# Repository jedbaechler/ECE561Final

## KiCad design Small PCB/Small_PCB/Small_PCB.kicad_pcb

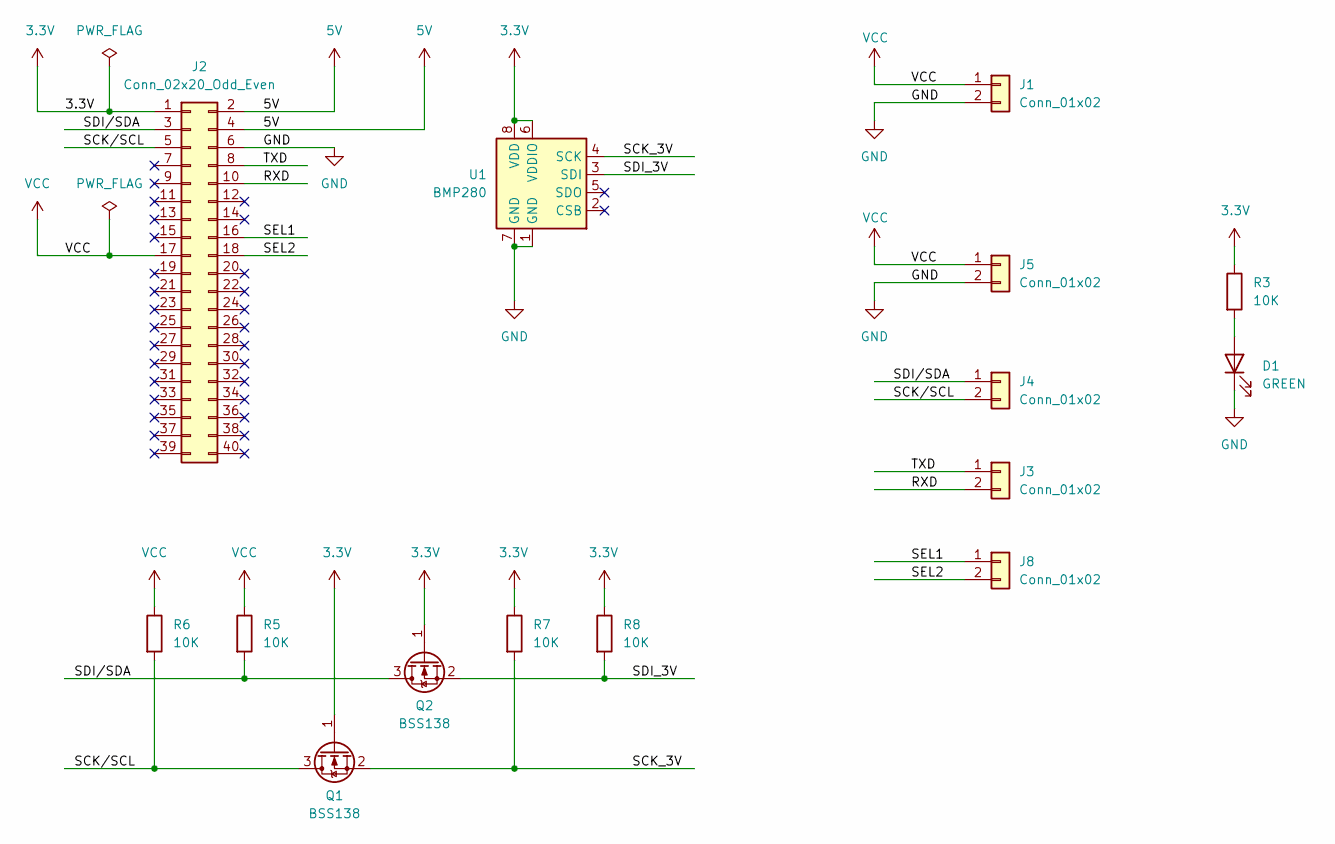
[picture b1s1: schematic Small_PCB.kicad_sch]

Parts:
D1: GREEN; LED_0805_2012Metric
J1, J3, J4, J5, J8: Conn_01x02; JST_EH_B2B-EH-A_1x02_P2.50mm_Vertical
J2: Conn_02x20_Odd_Even; PinSocket_2x20_P2.54mm_Vertical
Q1, Q2: BSS138; SOT-23
R3, R5, R6, R7, R8: 10K; R_0201_0603Metric
U1: BMP280; Bosch_LGA-8_2x2.5mm_P0.65mm_ClockwisePinNumbering

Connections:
3.3V: J2.1, Q1.1 (G), Q2.1 (G), R3.1, R7.1, R8.1, U1.6 (VDDIO), U1.8 (VDD)
5V: J2.2, J2.4
/RXD: J2.10, J3.2
/SCK_3V: Q1.2 (S), R7.2, U1.4 (SCK)
/SCK/SCL: J2.5, J4.2, Q1.3 (D), R6.2
/SDI_3V: Q2.2 (S), R8.2, U1.3 (SDI)
/SDI/SDA: J2.3, J4.1, Q2.3 (D), R5.2
/SEL1: J2.16, J8.1
/SEL2: J2.18, J8.2
/TXD: J2.8, J3.1
GND: D1.1 (K), J1.2, J2.6, J5.2, U1.1 (GND), U1.7 (GND)
unnamed: D1.2 (A), R3.2
VCC: J1.1, J2.17, J5.1, R5.1, R6.1

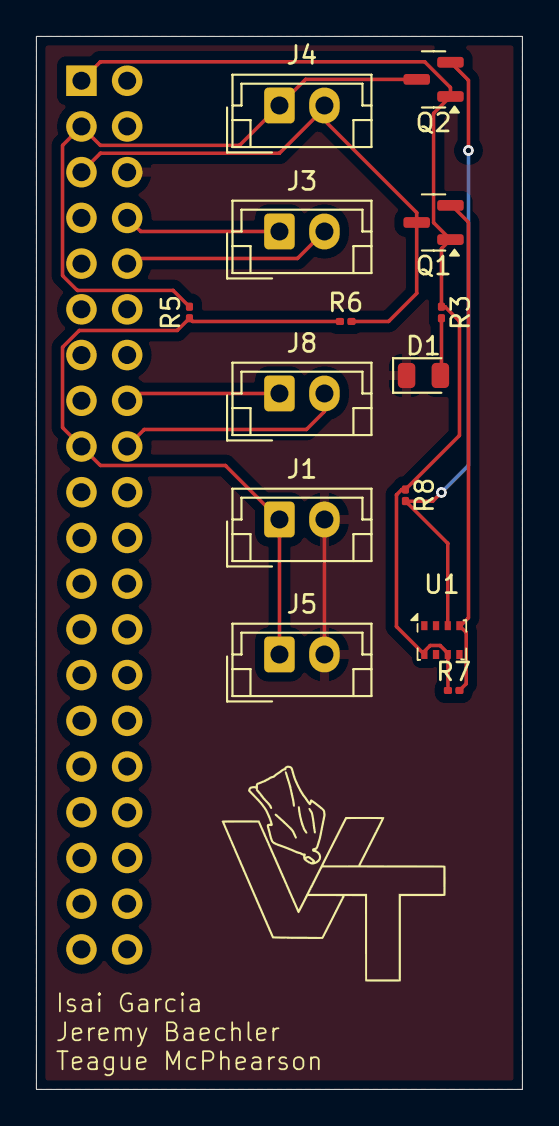
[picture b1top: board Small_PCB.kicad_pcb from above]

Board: 2 copper layers, 27.0 x 58.5 mm, 15 parts (1 on the bottom side), 13 nets.

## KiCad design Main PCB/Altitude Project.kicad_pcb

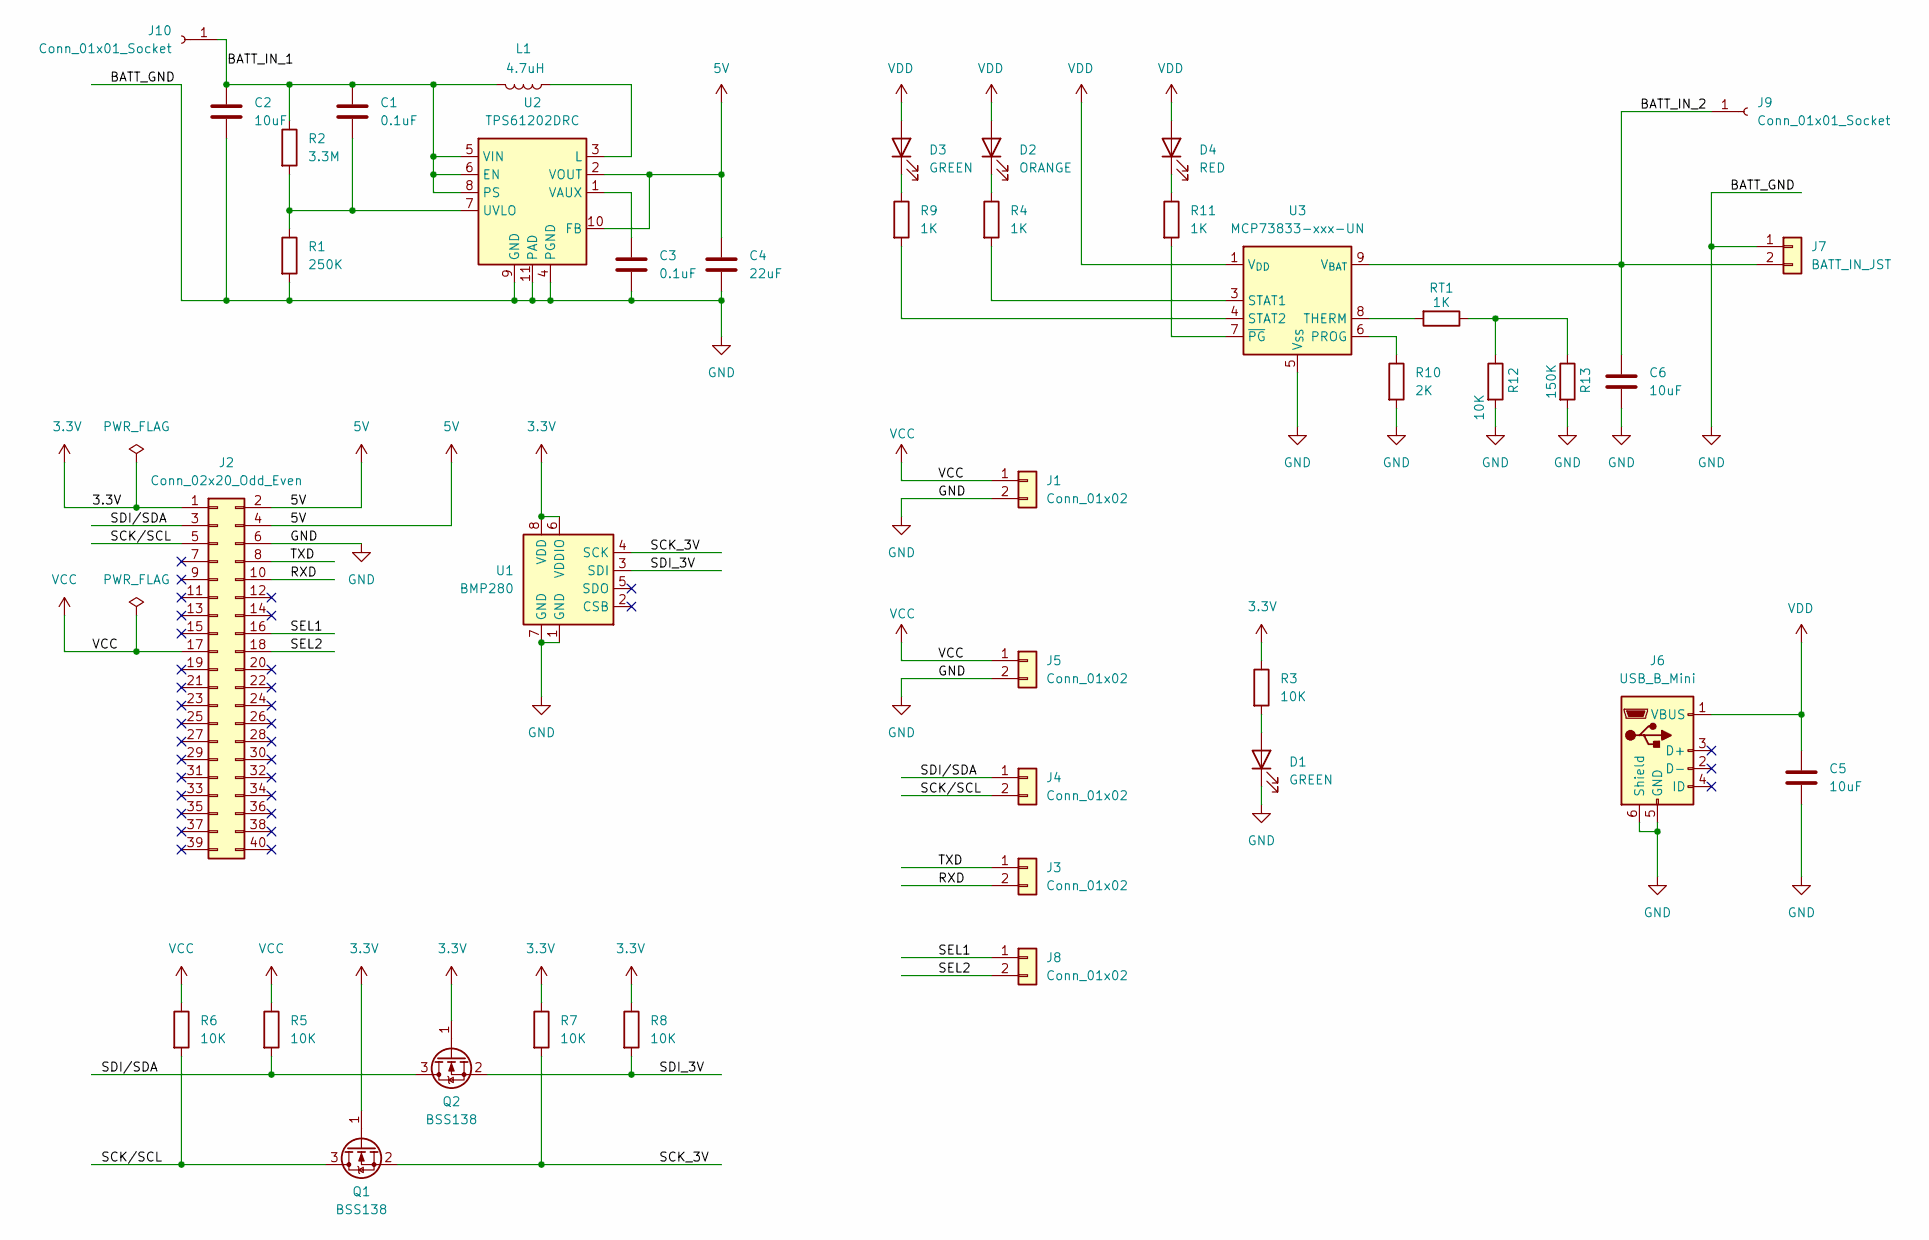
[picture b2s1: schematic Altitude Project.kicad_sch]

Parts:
C1, C3: 0.1uF; C_0402_1005Metric
C2, C5, C6: 10uF; C_0402_1005Metric
C4: 22uF; C_0402_1005Metric
D1, D3: GREEN; LED_0805_2012Metric
D2: ORANGE; LED_0805_2012Metric
D4: RED; LED_0805_2012Metric
J1, J3, J4, J5, J8: Conn_01x02; JST_EH_B2B-EH-A_1x02_P2.50mm_Vertical
J2: Conn_02x20_Odd_Even; PinSocket_2x20_P2.54mm_Vertical
J6: USB_B_Mini; USB_Mini-B_Lumberg_2486_01_Horizontal
J7: BATT_IN_JST; JST_EH_S2B-EH_1x02_P2.50mm_Horizontal
J9, J10: Conn_01x01_Socket; TestPoint_THTPad_2.0x2.0mm_Drill1.0mm
L1: 4.7uH; L_Changjiang_FNR4020S
Q1, Q2: BSS138; SOT-23
R1: 250K; R_0201_0603Metric
R2: 3.3M; R_1206_3216Metric
R3, R5, R6, R7, R8, R12: 10K; R_0201_0603Metric
R4, R9, R11: 1K; R_0201_0603Metric
R10: 2K; R_0201_0603Metric
R13: 150K; R_0201_0603Metric
RT1: 1K; R_0201_0603Metric
U1: BMP280; Bosch_LGA-8_2x2.5mm_P0.65mm_ClockwisePinNumbering
U2: TPS61202DRC; Texas_S-PVSON-N10_ThermalVias
U3: MCP73833-xxx-UN; MSOP-10_3x3mm_P0.5mm

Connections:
3.3V: J2.1, Q1.1 (G), Q2.1 (G), R3.1, R7.1, R8.1, U1.6 (VDDIO), U1.8 (VDD)
5V: C4.1, J2.2, J2.4, U2.2 (VOUT), U2.10 (FB)
/BATT_IN_1: C1.1, C2.1, J10.1, L1.2, R2.1, U2.5 (VIN), U2.6 (EN), U2.8 (PS)
/BATT_IN_2: C6.1, J7.2, J9.1, U3.9 (V_{BAT}), U3.10 (V_{BAT})
/RXD: J2.10, J3.2
/SCK_3V: Q1.2 (S), R7.2, U1.4 (SCK)
/SCK/SCL: J2.5, J4.2, Q1.3 (D), R6.2
/SDI_3V: Q2.2 (S), R8.2, U1.3 (SDI)
/SDI/SDA: J2.3, J4.1, Q2.3 (D), R5.2
/SEL1: J2.16, J8.1
/SEL2: J2.18, J8.2
/TXD: J2.8, J3.1
GND: C2.2, C3.2, C4.2, C5.2, C6.2, D1.1 (K), J1.2, J2.6, J5.2, J6.5 (GND), J6.6 (Shield), J7.1, R1.2, R10.2, R12.2, R13.2, U1.1 (GND), U1.7 (GND), U2.4 (PGND), U2.9 (GND), U2.11 (PAD), U3.5 (V_{SS})
unnamed: D1.2 (A), R3.2
unnamed: D2.1 (K), R4.1
unnamed: D3.1 (K), R9.1
unnamed: D4.1 (K), R11.1
unnamed: R12.1, R13.1, RT1.1
unnamed: L1.1, U2.3 (L)
unnamed: C1.2, R1.1, R2.2, U2.7 (UVLO)
unnamed: C3.1, U2.1 (VAUX)
unnamed: R10.1, U3.6 (PROG)
unnamed: R4.2, U3.3 (STAT1)
unnamed: R9.2, U3.4 (STAT2)
unnamed: RT1.2, U3.8 (THERM)
unnamed: R11.2, U3.7 (~PG)
VCC: J1.1, J2.17, J5.1, R5.1, R6.1
VDD: C5.1, D2.2 (A), D3.2 (A), D4.2 (A), J6.1 (VBUS), U3.1 (V_{DD}), U3.2 (V_{DD})

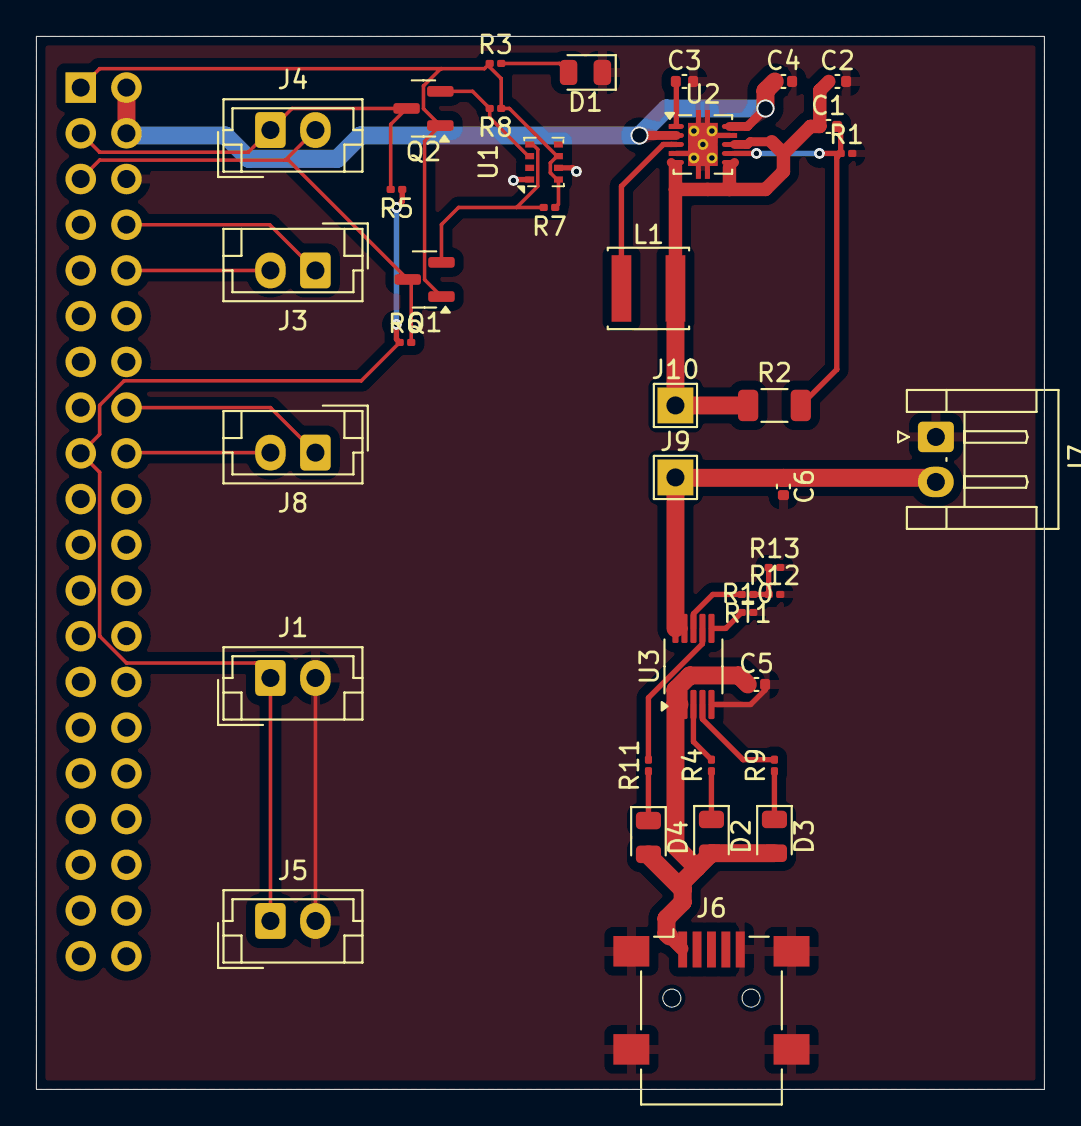
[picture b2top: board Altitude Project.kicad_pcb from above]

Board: 2 copper layers, 56.0 x 58.5 mm, 40 parts (1 on the bottom side), 28 nets.

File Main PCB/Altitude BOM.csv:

"Id";"Designator";"Footprint";"Quantity";"Designation";"Supplier and ref";
1;"U2";"Texas_S-PVSON-N10_ThermalVias";1;"TPS61202DRC";;;
2;"J9,J10";"TestPoint_THTPad_2.0x2.0mm_Drill1.0mm";2;"Conn_01x01_Socket";;;
3;"U3";"MSOP-10_3x3mm_P0.5mm";1;"MCP73833-xxx-UN";;;
4;"C3,C1";"C_0402_1005Metric";2;"0.1uF";;;
5;"R13";"R_0201_0603Metric";1;"150K";;;
6;"L1";"L_Changjiang_FNR4020S";1;"4.7uH";;;
7;"R12,R5,R8,R7,R3,R6";"R_0201_0603Metric";6;"10K";;;
8;"J7";"JST_EH_S2B-EH_1x02_P2.50mm_Horizontal";1;"BATT_IN_JST";;;
9;"U1";"Bosch_LGA-8_2x2.5mm_P0.65mm_ClockwisePinNumbering";1;"BMP280";;;
10;"Q1,Q2";"SOT-23";2;"BSS138";;;
11;"J8,J5,J1,J3,J4";"JST_EH_B2B-EH-A_1x02_P2.50mm_Vertical";5;"Conn_01x02";;;
12;"R4,R11,RT1,R9";"R_0201_0603Metric";4;"1K";;;
13;"R2";"R_1206_3216Metric";1;"3.3M";;;
14;"D3,D1";"LED_0805_2012Metric";2;"GREEN";;;
15;"C4";"C_0402_1005Metric";1;"22uF";;;
16;"D2";"LED_0805_2012Metric";1;"ORANGE";;;
17;"C6,C5,C2";"C_0402_1005Metric";3;"10uF";;;
18;"D4";"LED_0805_2012Metric";1;"RED";;;
19;"R10";"R_0201_0603Metric";1;"2K";;;
20;"R1";"R_0201_0603Metric";1;"250K";;;
21;"J6";"USB_Mini-B_Lumberg_2486_01_Horizontal";1;"USB_B_Mini";;;
22;"J2";"PinSocket_2x20_P2.54mm_Vertical";1;"Conn_02x20_Odd_Even";;;

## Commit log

2024-05-05 Final Code and Schematic Upload
2024-05-05 Suppl. Materials
2024-05-05 final submission
2024-05-05 included links in final report
